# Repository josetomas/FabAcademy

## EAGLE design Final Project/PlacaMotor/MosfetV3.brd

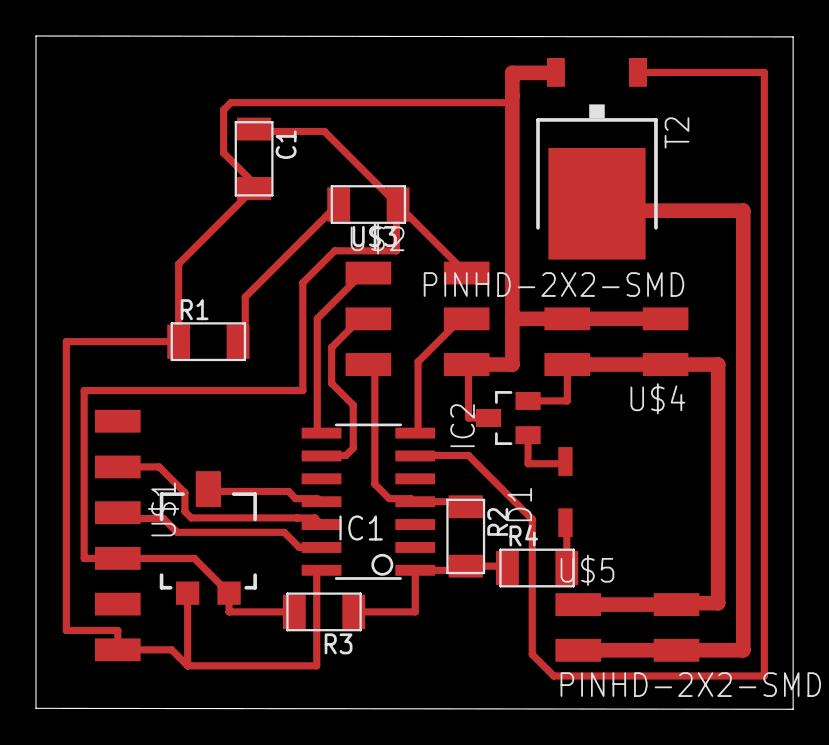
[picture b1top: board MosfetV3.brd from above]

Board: 2 copper layers, 42.1 x 37.4 mm, 15 parts (0 on the bottom side), 14 nets.

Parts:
C1: 1uF; C1206FAB
D1: SOD123
IC1: ATTINY44-SSU; SOIC14
IC2: SOT23
R1: 499; R1206FAB
R2: 10K; R1206FAB
R3, R4: 0; R1206FAB
T2: TO252
U$1: FTDI-SMD-HEADER; 1X06SMD
U$2: AVRISPSMD; 2X03SMD
U$3: LEDFAB1206; LED1206FAB
U$4, U$5: PINHD-2X2-SMD; 2X02SMD
VR1: 5k; TRIMPOT-SMD-5MM

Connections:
0: C1.2, IC1.14, IC2.3, R1.1, T2.2, U$1.1, U$2.6, U$4.3, U$4.4, VR1.C
12V: IC2.2, U$4.1, U$4.2, U$5.1, U$5.2
ANALOG: IC1.11, VR1.B
MISO: IC1.8, U$2.1
MOSFET: T2.3, U$5.3, U$5.4
MOSI: IC1.7, U$2.4
MOTOR: IC1.6, T2.1
unnamed: R1.2, U$3.2
unnamed: D1.ANODE, IC2.1
RST: IC1.4, R2.1, U$2.5
RX: IC1.12, U$1.5
SCK: IC1.9, U$2.3
TX: IC1.13, U$1.4
VCC: C1.1, D1.CATHODE, IC1.1, R2.2, R3.1, R3.2, R4.1, R4.2, U$1.3, U$2.2, U$3.1, VR1.A

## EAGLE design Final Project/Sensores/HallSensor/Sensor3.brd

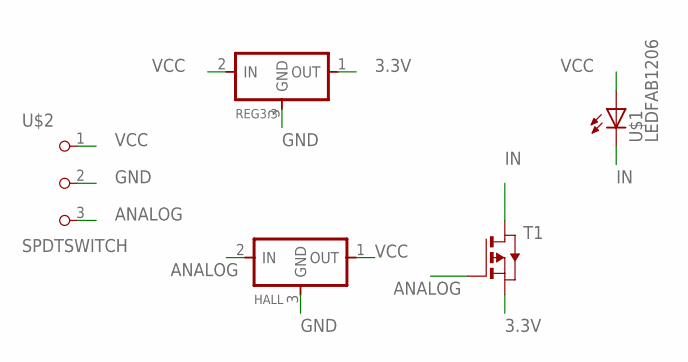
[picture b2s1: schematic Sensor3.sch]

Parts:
HALL: REGULATORSOT23; SOT23
REG3.3: REGULATORSOT23; SOT23
T1: PMOSFETSOT23; SOT-23
U$1: LEDFAB1206; LED1206FAB
U$2: SPDTSWITCH

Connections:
3.3V: REG3.3.1 (OUT), T1.2 (S)
ANALOG: HALL.2 (IN), T1.3 (G), U$2.3
GND: HALL.3 (GND), REG3.3.3 (GND), U$2.2
IN: T1.1 (D), U$1.2 (C)
VCC: HALL.1 (OUT), REG3.3.2 (IN), U$1.1 (A), U$2.1

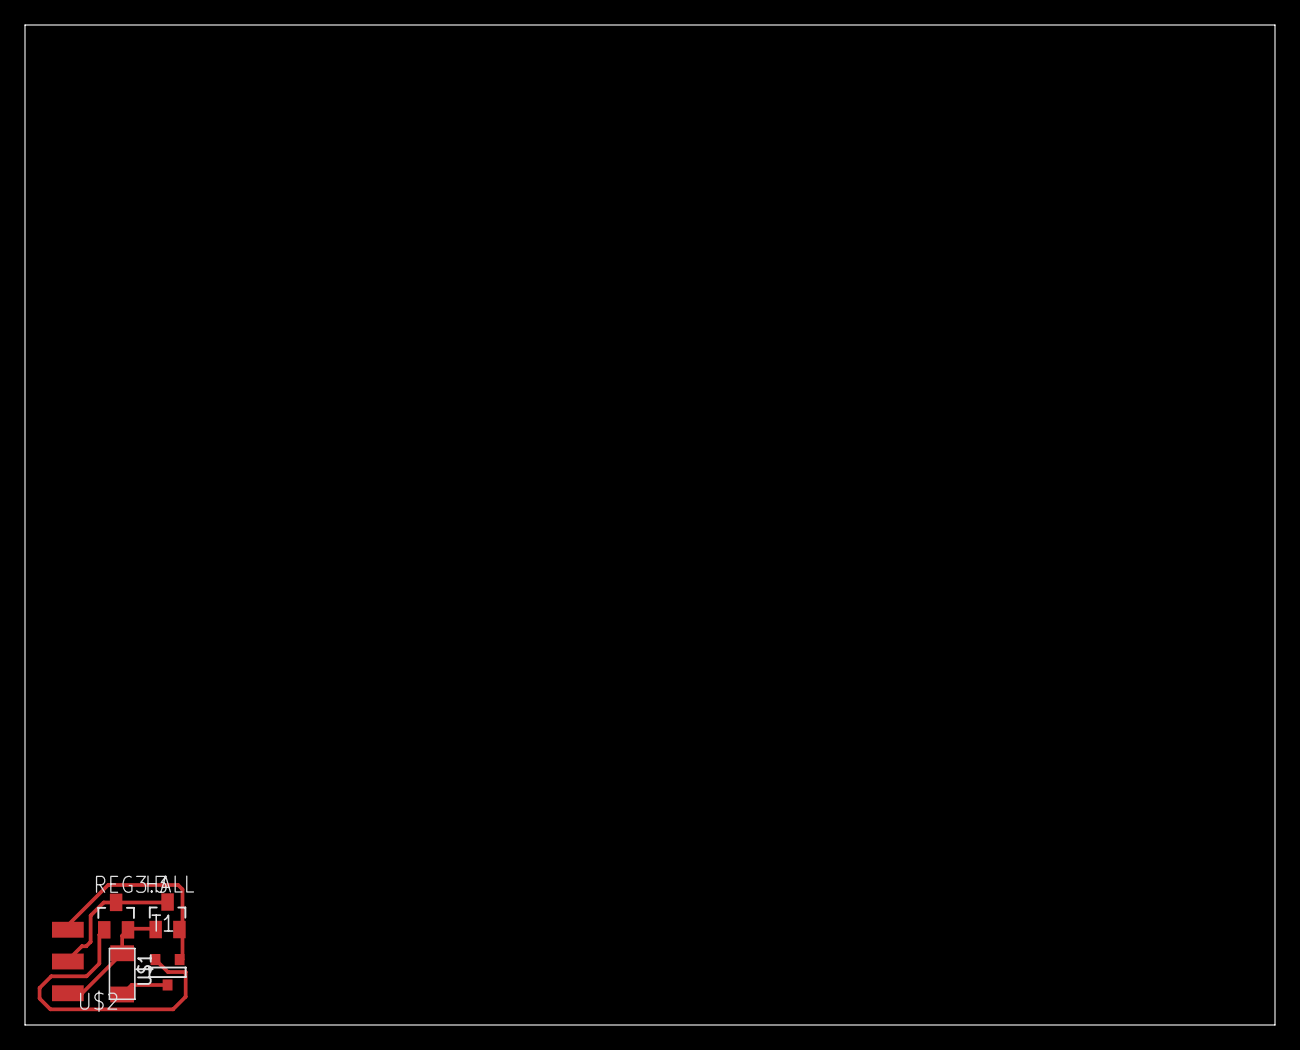
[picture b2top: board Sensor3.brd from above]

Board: 2 copper layers, 100.0 x 80.0 mm, 5 parts (0 on the bottom side), 5 nets.

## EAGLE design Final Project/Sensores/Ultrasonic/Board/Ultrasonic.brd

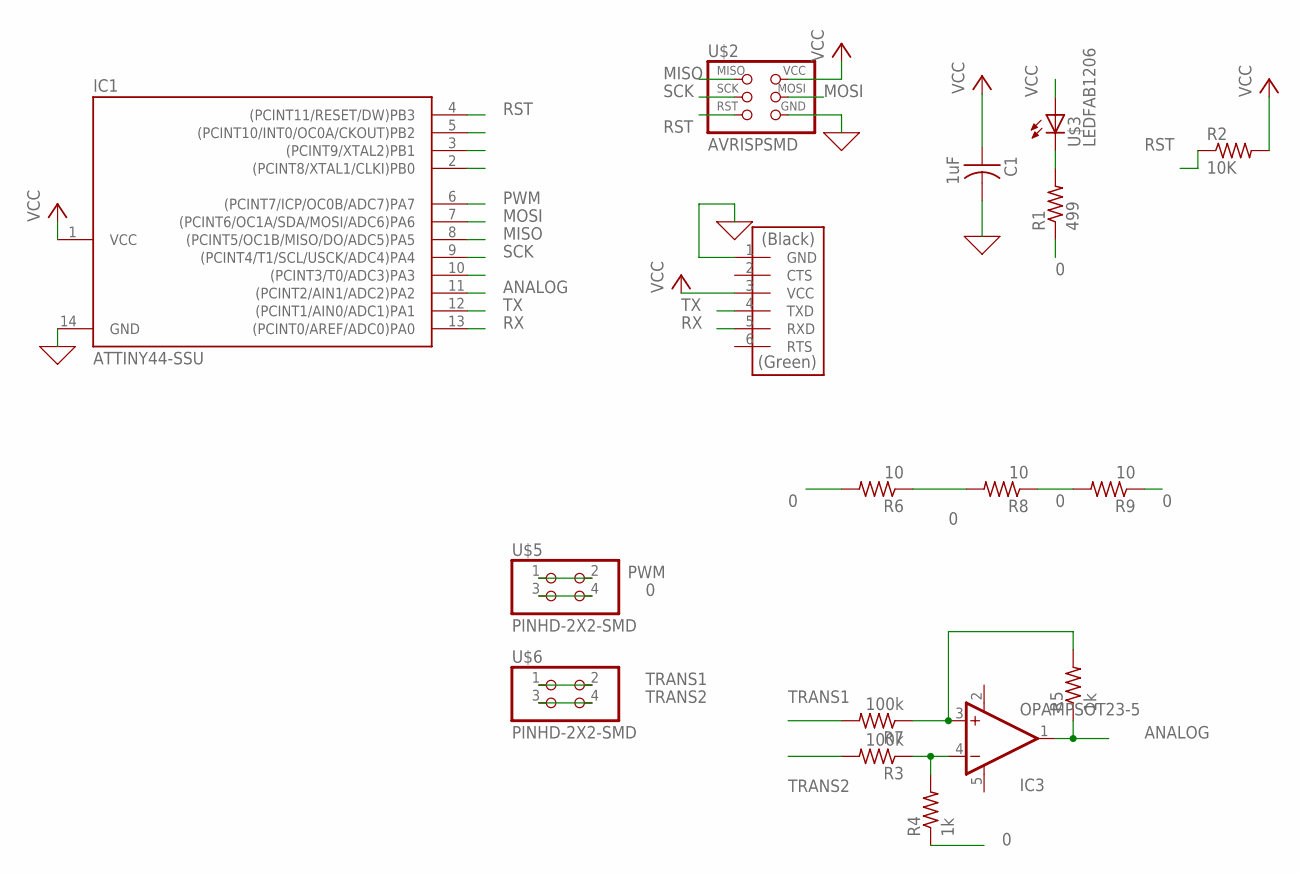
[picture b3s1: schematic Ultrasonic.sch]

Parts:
C1: 1uF; C1206FAB
IC1: ATTINY44-SSU; SOIC14
IC3: OPAMPSOT23-5; SOT23-5
R1: 499; R1206FAB
R2: 10K; R1206FAB
R3, R7: 100k; R1206FAB
R4, R5: 1k; R1206FAB
R6, R8, R9: 10; R1206FAB
U$1: FTDI-SMD-HEADER; 1X06SMD
U$2: AVRISPSMD; 2X03SMD
U$3: LEDFAB1206; LED1206FAB
U$5, U$6: PINHD-2X2-SMD; 2X02SMD

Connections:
0: C1.2, IC1.14 (GND), R1.1, R4.1, R6.1, R6.2, R8.1, R8.2, R9.1, R9.2, U$1.1 (GND), U$2.6 (GND), U$5.3, U$5.4
ANALOG: IC1.11 ((PCINT2/AIN1/ADC2)PA2), IC3.1 (OUT), R5.1
MISO: IC1.8 ((PCINT5/OC1B/MISO/DO/ADC5)PA5), U$2.1 (MISO)
MOSI: IC1.7 ((PCINT6/OC1A/SDA/MOSI/ADC6)PA6), U$2.4 (MOSI)
unnamed: R1.2, U$3.2 (C)
unnamed: IC3.3 (+IN), R5.2, R7.1
unnamed: IC3.4 (-IN), R3.1, R4.2
PWM: IC1.6 ((PCINT7/ICP/OC0B/ADC7)PA7), U$5.1, U$5.2
RST: IC1.4 ((PCINT11/RESET/DW)PB3), R2.1, U$2.5 (RST)
RX: IC1.13 ((PCINT0/AREF/ADC0)PA0), U$1.5 (RXD)
SCK: IC1.9 ((PCINT4/T1/SCL/USCK/ADC4)PA4), U$2.3 (SCK)
TRANS1: R7.2, U$6.1, U$6.2
TRANS2: R3.2, U$6.3, U$6.4
TX: IC1.12 ((PCINT1/AIN0/ADC1)PA1), U$1.4 (TXD)
V+: IC3.5 (V+)
V-: IC3.2 (V-)
VCC: C1.1, IC1.1 (VCC), R2.2, U$1.3 (VCC), U$2.2 (VCC), U$3.1 (A)

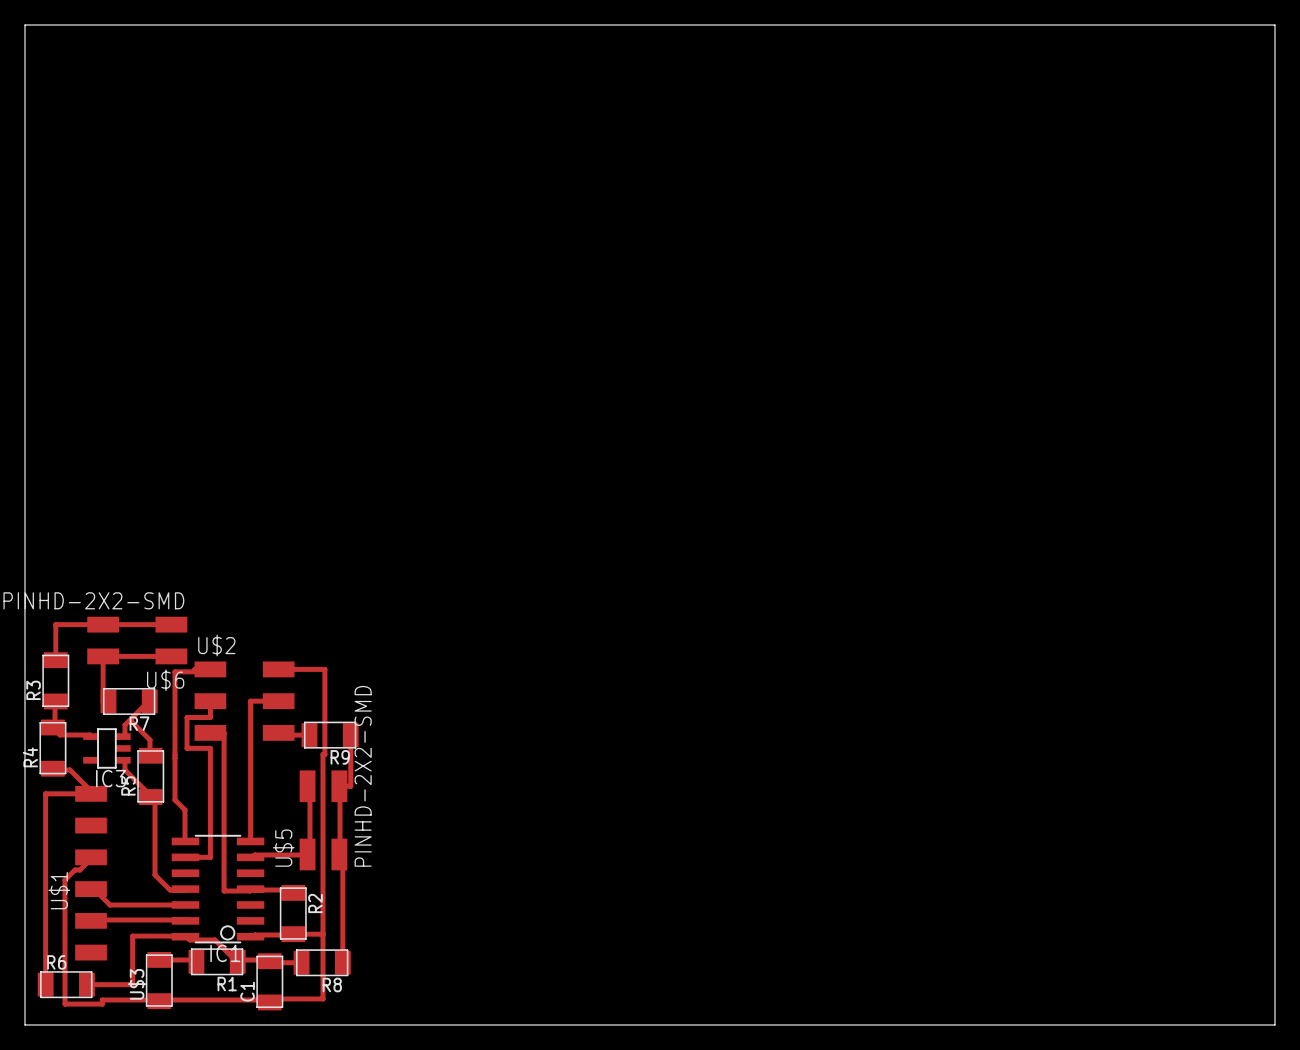
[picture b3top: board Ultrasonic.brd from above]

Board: 2 copper layers, 100.0 x 80.0 mm, 17 parts (0 on the bottom side), 15 nets.

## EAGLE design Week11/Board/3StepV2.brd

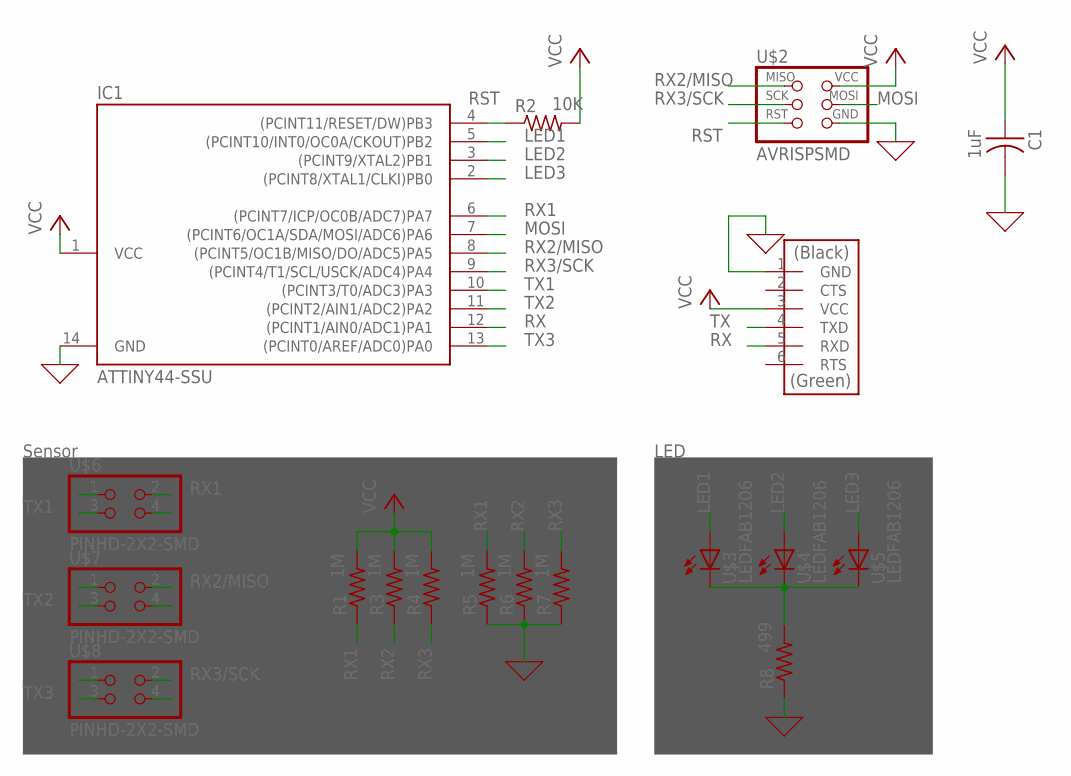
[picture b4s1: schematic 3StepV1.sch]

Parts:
C1: 1uF; C1206FAB
IC1: ATTINY44-SSU; SOIC14
R1, R3, R4, R5, R6, R7: 1M; R1206FAB
R2: 10K; R1206FAB
R8: 499; R1206FAB
U$1: FTDI-SMD-HEADER; 1X06SMD
U$2: AVRISPSMD; 2X03SMD
U$3, U$4, U$5: LEDFAB1206; LED1206FAB
U$6, U$7, U$8: PINHD-2X2-SMD; 2X02SMD

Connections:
0: C1.2, IC1.14 (GND), R5.1, R6.1, R7.1, R8.1, U$1.1 (GND), U$2.6 (GND)
LED1: IC1.5 ((PCINT10/INT0/OC0A/CKOUT)PB2), U$3.1 (A)
LED2: IC1.3 ((PCINT9/XTAL2)PB1), U$4.1 (A)
LED3: IC1.2 ((PCINT8/XTAL1/CLKI)PB0), U$5.1 (A)
MOSI: IC1.7 ((PCINT6/OC1A/SDA/MOSI/ADC6)PA6), U$2.4 (MOSI)
unnamed: R8.2, U$3.2 (C), U$4.2 (C), U$5.2 (C)
RST: IC1.4 ((PCINT11/RESET/DW)PB3), R2.1, U$2.5 (RST)
RX: IC1.12 ((PCINT1/AIN0/ADC1)PA1), U$1.5 (RXD)
RX1: IC1.6 ((PCINT7/ICP/OC0B/ADC7)PA7), R1.1, R5.2, U$6.2
RX2: R3.1, R6.2
RX2/MISO: IC1.8 ((PCINT5/OC1B/MISO/DO/ADC5)PA5), U$2.1 (MISO), U$7.2
RX3: R4.1, R7.2
RX3/SCK: IC1.9 ((PCINT4/T1/SCL/USCK/ADC4)PA4), U$2.3 (SCK), U$8.2
TX: U$1.4 (TXD)
TX1: IC1.10 ((PCINT3/T0/ADC3)PA3), U$6.3
TX2: IC1.11 ((PCINT2/AIN1/ADC2)PA2), U$7.3
TX3: IC1.13 ((PCINT0/AREF/ADC0)PA0), U$8.3
VCC: C1.1, IC1.1 (VCC), R1.2, R2.2, R3.2, R4.2, U$1.3 (VCC), U$2.2 (VCC)

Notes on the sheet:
Sensor
LED

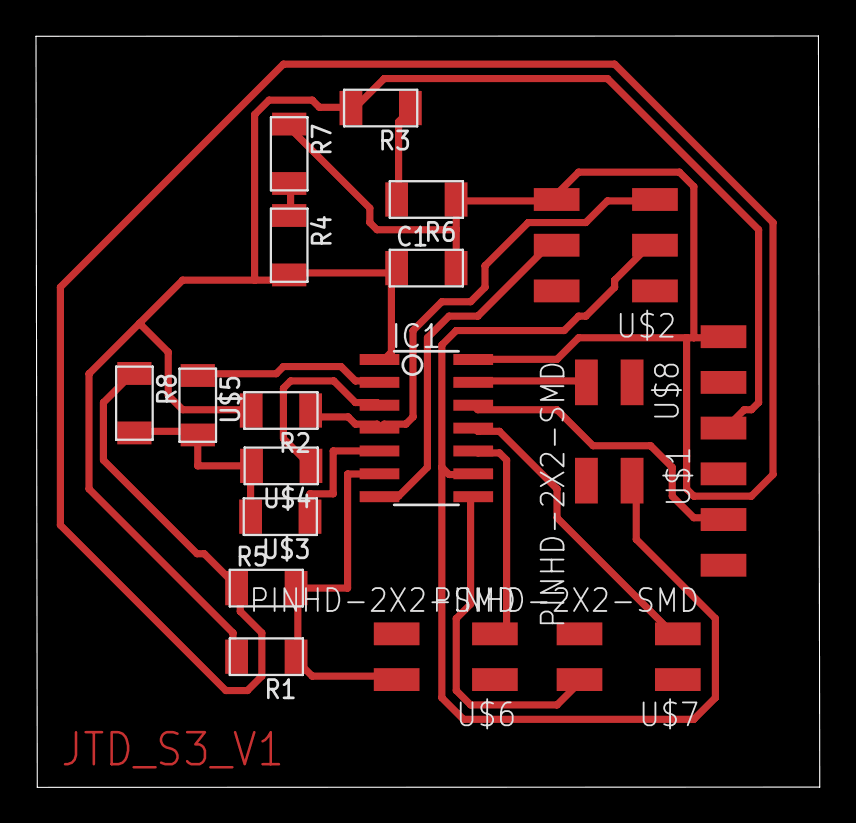
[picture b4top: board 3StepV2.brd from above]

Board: 2 copper layers, 43.5 x 41.7 mm, 18 parts (0 on the bottom side), 17 nets.

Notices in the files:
parts and their libraries:
SparkFun-Resistors: Licensing: Creative Commons ShareAlike 4.0 International - https://creativecommons.org/licenses/by-sa/4.0
